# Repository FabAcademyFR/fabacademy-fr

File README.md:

# fabacademy-fr
Studenti Fab Academy 2015 - FabLab Frosinone
hello world

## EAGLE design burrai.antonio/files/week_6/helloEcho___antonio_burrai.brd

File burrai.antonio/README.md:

# fabacademy-fr
Studenti Fabacademy 2015 - FabLab Frosinone
Cartella personale di Antonio Burrai

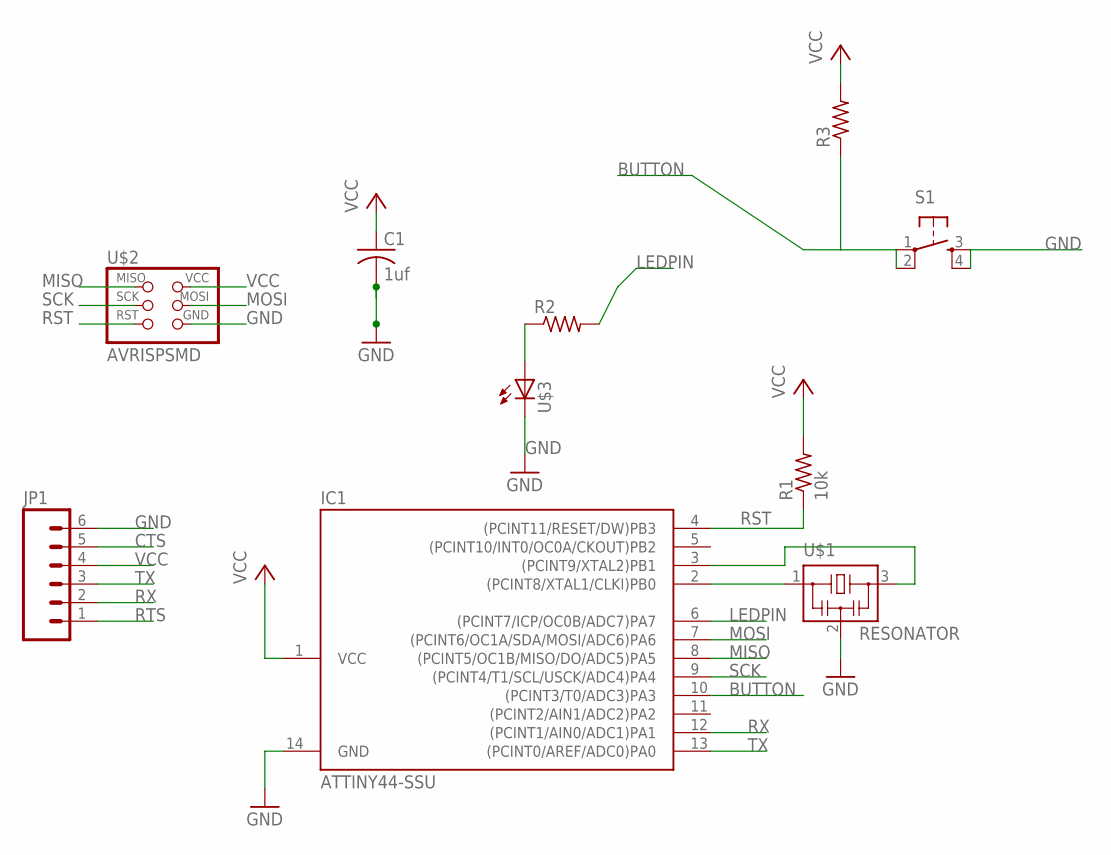
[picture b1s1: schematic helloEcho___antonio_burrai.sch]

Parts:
C1: 1uf; C1206
IC1: ATTINY44-SSU; SOIC14
JP1: M06SMD; 1X06-SMD
R1: 10k; R1206
R2, R3: RESISTOR1206; 1206
S1: 6MM_SWITCH6MM_SWITCH; 6MM_SWITCH
U$1: RESONATOR; EFOBM
U$2: AVRISPSMD; 2X03SMD
U$3: LED1206; 1206

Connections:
BUTTON: IC1.10 ((PCINT3/T0/ADC3)PA3), R3.1, S1.1, S1.2 (P1)
CTS: JP1.5
GND: C1.2, IC1.14 (GND), JP1.6, S1.3 (S), S1.4 (S1), U$1.2, U$2.6 (GND), U$3.2 (C)
LEDPIN: IC1.6 ((PCINT7/ICP/OC0B/ADC7)PA7), R2.2
MISO: IC1.8 ((PCINT5/OC1B/MISO/DO/ADC5)PA5), U$2.1 (MISO)
MOSI: IC1.7 ((PCINT6/OC1A/SDA/MOSI/ADC6)PA6), U$2.4 (MOSI)
unnamed: IC1.2 ((PCINT8/XTAL1/CLKI)PB0), U$1.1
unnamed: IC1.3 ((PCINT9/XTAL2)PB1), U$1.3
unnamed: R2.1, U$3.1 (A)
RST: IC1.4 ((PCINT11/RESET/DW)PB3), R1.1, U$2.5 (RST)
RTS: JP1.1
RX: IC1.12 ((PCINT1/AIN0/ADC1)PA1), JP1.2
SCK: IC1.9 ((PCINT4/T1/SCL/USCK/ADC4)PA4), U$2.3 (SCK)
TX: IC1.13 ((PCINT0/AREF/ADC0)PA0), JP1.3
VCC: C1.1, IC1.1 (VCC), JP1.4, R1.2, R3.2, U$2.2 (VCC)

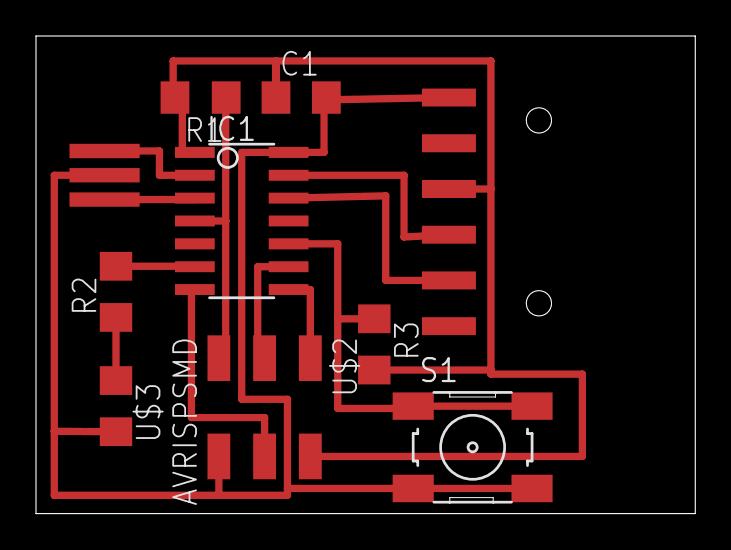
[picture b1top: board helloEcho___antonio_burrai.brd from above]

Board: 1 copper layer, 36.6 x 26.5 mm, 10 parts (0 on the bottom side), 13 nets.

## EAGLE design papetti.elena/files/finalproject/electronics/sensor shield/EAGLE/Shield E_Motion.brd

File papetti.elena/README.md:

# fabacademy-fr
Studenti Fabacademy 2015 - FabLab Frosinone
Cartella personale di Papetti Elena
hello

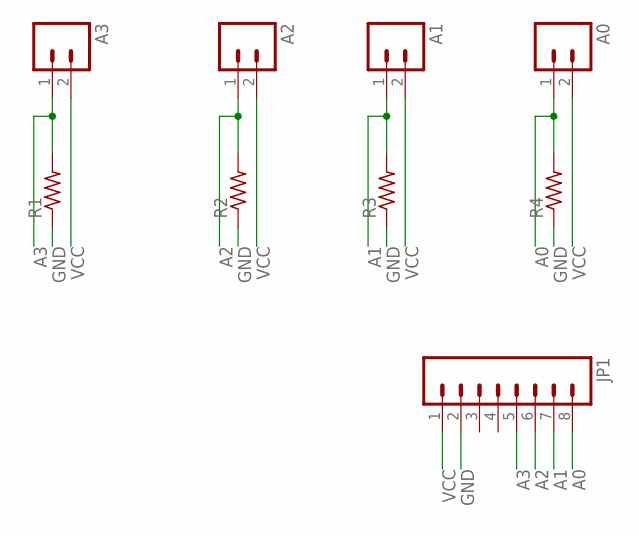
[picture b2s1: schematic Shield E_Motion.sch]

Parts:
A0, A1, A2, A3: M02; 1X02_LONGPADS
JP1: M08LONGPADS; 1X08_LONGPADS
R1, R2, R3, R4: RESISTOR0402; 0402

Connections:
A0: A0.1, JP1.8, R4.2
A1: A1.1, JP1.7, R3.2
A2: A2.1, JP1.6, R2.2
A3: A3.1, JP1.5, R1.2
GND: JP1.2, R1.1, R2.1, R3.1, R4.1
VCC: A0.2, A1.2, A2.2, A3.2, JP1.1

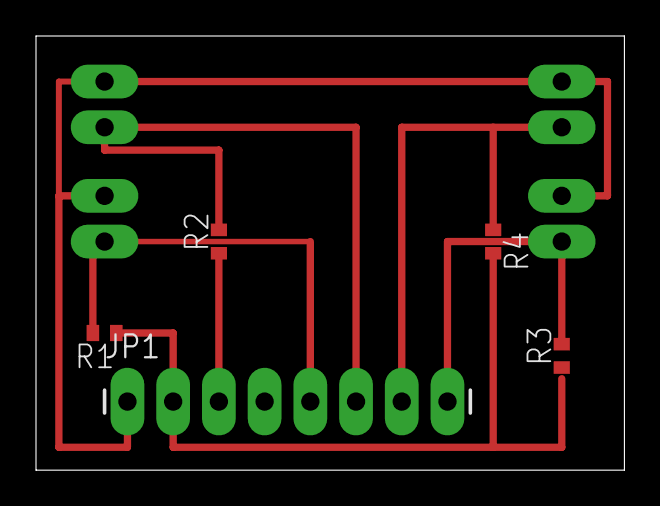
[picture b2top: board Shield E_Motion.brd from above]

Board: 2 copper layers, 32.7 x 24.1 mm, 9 parts (0 on the bottom side), 6 nets.

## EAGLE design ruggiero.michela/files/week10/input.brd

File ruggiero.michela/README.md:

# fabacademy-fr
Studenti Fabacademy 2015 - FabLab Frosinone
Cartella personale di Ruggiero Michela

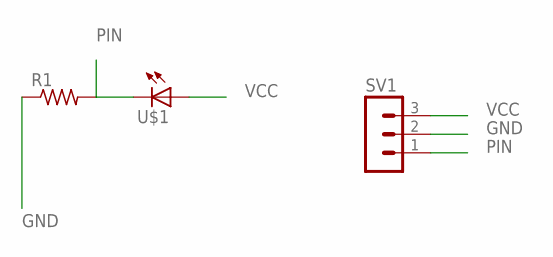
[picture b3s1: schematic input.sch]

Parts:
R1: RESISTOR1206; 1206
SV1: MA03-1
U$1: LED5MM; 5MM

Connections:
GND: R1.1, SV1.2
PIN: R1.2, SV1.1, U$1.OUT (C)
VCC: SV1.3, U$1.IN (A)

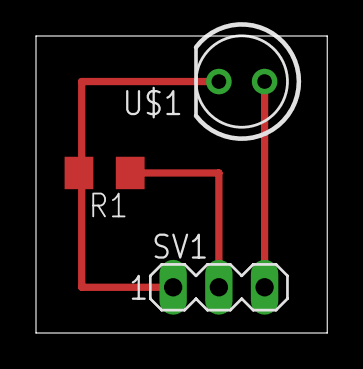
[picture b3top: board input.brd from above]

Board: 2 copper layers, 16.2 x 16.5 mm, 3 parts (0 on the bottom side), 3 nets.

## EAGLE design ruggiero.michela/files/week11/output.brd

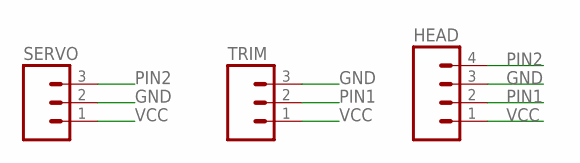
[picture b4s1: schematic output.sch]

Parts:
HEAD: M04LONGPADS; 1X04_LONGPADS
SERVO: M03PTH; 1X03
TRIM: M03PTH; 1X03

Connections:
GND: HEAD.3, SERVO.2, TRIM.3
PIN1: HEAD.2, TRIM.2
PIN2: HEAD.4, SERVO.3
VCC: HEAD.1, SERVO.1, TRIM.1

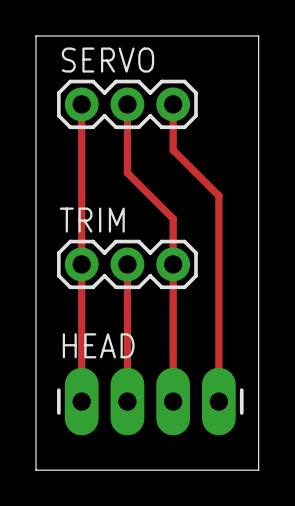
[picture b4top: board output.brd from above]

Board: 2 copper layers, 12.4 x 24.1 mm, 3 parts (0 on the bottom side), 4 nets.

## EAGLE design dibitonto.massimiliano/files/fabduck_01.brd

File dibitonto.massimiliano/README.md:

# fabacademy-fr
Studenti Fabacademy 2015 - FabLab Frosinone
Cartella personale di Dibitonto Massimiliano

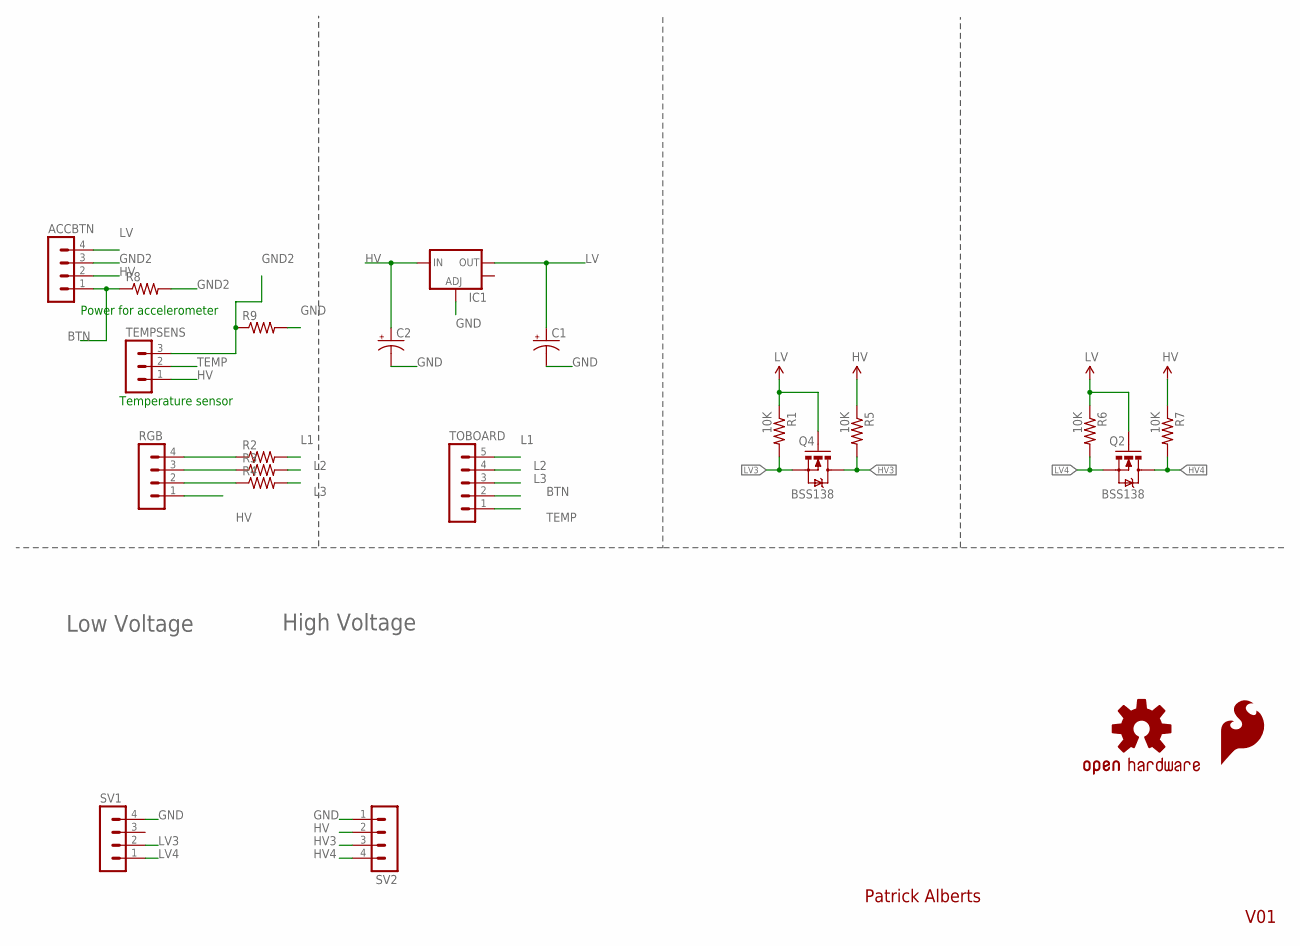
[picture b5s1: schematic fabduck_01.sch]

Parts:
ACCBTN: MA04-1
C1, C2: CAP_POLD; PANASONIC_D
IC1: V_REG_LM1117SOT223; SOT223
LOGO1: SFE_LOGO_FLAME.1_INCH; SFE_LOGO_FLAME_.1
LOGO2: OSHW-LOGOS; OSHW-LOGO-S
Q2, Q4: BSS138; SOT23-3
R1, R5, R6, R7: 10K; 0603-RES
R2, R3, R4, R8, R9: RESISTOR1206; 1206
RGB: MA04-1
SV1, SV2: MA04-1
TEMPSENS: MA03-1
TOBOARD: MA05-1

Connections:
BTN: ACCBTN.1, R8.1, TOBOARD.2
GND: C1.-, C2.-, IC1.1 (ADJ), R9.2, SV1.4, SV2.1
GND2: ACCBTN.3, R8.2, R9.1, TEMPSENS.3
HV: ACCBTN.2, C2.+, IC1.3 (IN), R5.1, R7.1, RGB.1, SV2.2, TEMPSENS.1
HV3: Q4.3 (D), R5.2, SV2.3
HV4: Q2.3 (D), R7.2, SV2.4
L1: R2.2, TOBOARD.5
L2: R3.2, TOBOARD.4
L3: R4.2, TOBOARD.3
LV: ACCBTN.4, C1.+, IC1.2 (OUT), Q2.1 (G), Q4.1 (G), R1.1, R6.1
LV3: Q4.2 (S), R1.2, SV1.2
LV4: Q2.2 (S), R6.2, SV1.1
unnamed: R3.1, RGB.3
unnamed: R4.1, RGB.2
unnamed: R2.1, RGB.4
TEMP: TEMPSENS.2, TOBOARD.1

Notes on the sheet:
High Voltage
Low Voltage
V01
Patrick Alberts
Power for accelerometer
Temperature sensor

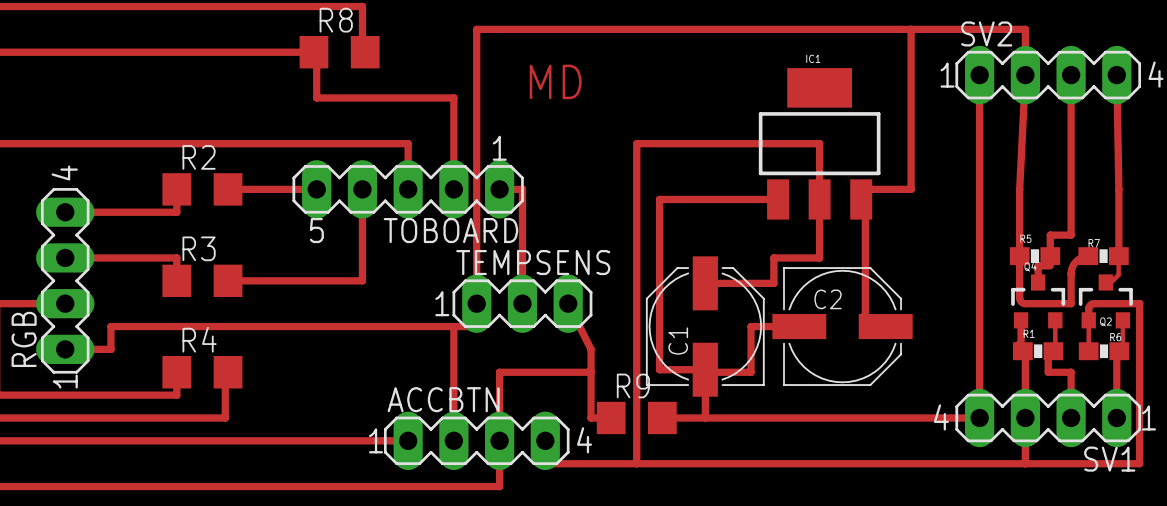
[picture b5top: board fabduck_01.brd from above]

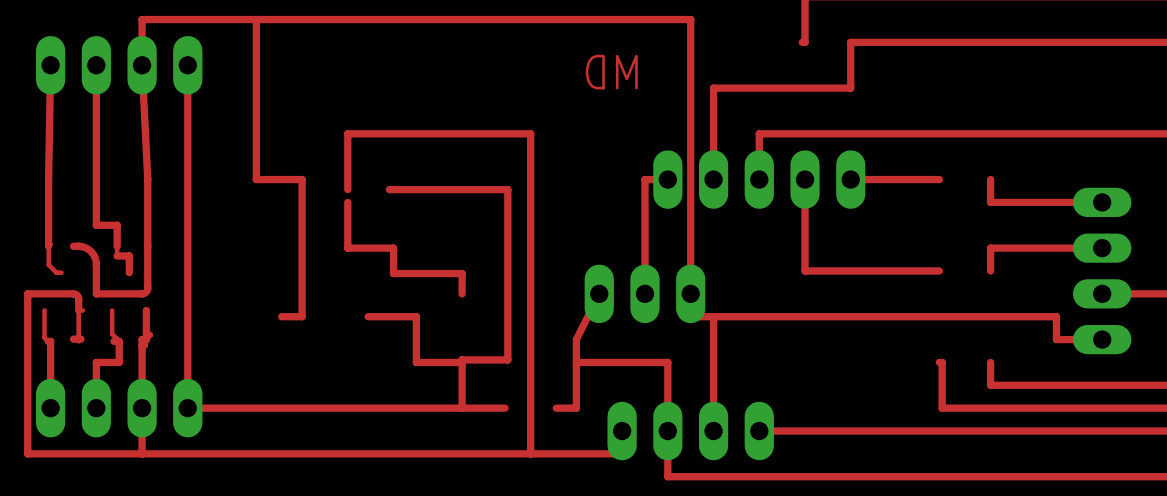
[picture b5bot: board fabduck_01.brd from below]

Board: 2 copper layers, 22 parts (2 on the bottom side), 16 nets.

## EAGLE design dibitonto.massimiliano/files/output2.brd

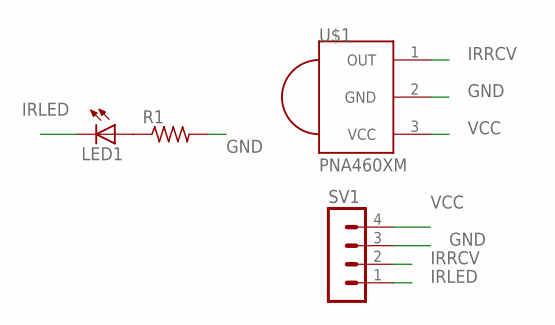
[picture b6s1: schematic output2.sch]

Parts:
LED1: LED5MM
R1: RESISTOR1206; 1206
SV1: MA04-1
U$1: PNA460XM

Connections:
GND: R1.2, SV1.3, U$1.2 (GND)
IRLED: LED1.K (C), SV1.1
IRRCV: SV1.2, U$1.1 (OUT)
LDR: LED1.A, R1.1
VCC: SV1.4, U$1.3 (VCC)

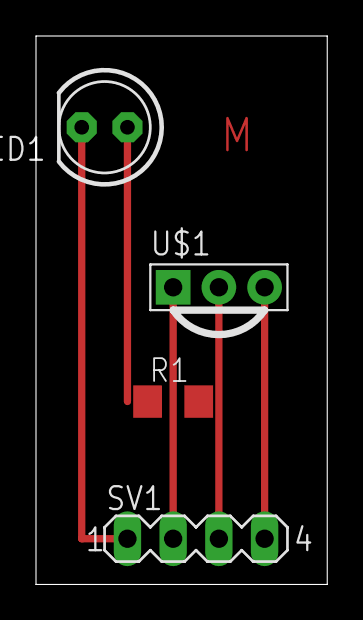
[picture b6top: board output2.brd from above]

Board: 2 copper layers, 16.2 x 30.5 mm, 4 parts (0 on the bottom side), 5 nets.

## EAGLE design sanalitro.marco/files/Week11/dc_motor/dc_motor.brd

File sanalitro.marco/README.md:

# fabacademy-fr
Studenti Fabacademy 2015 - FabLab Frosinone
Cartella personale di Sanalitro Marco

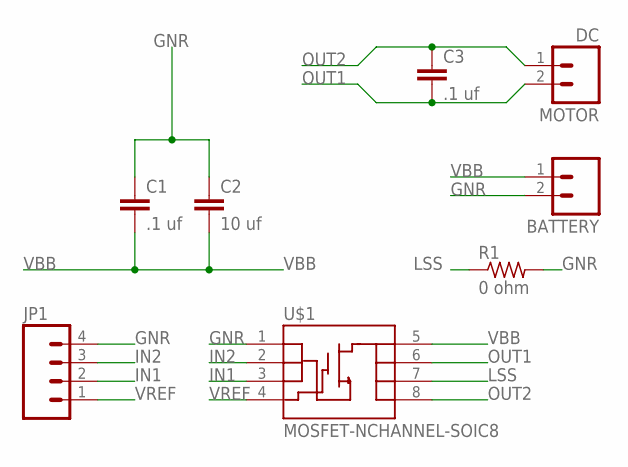
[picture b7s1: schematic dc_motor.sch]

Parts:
BATTERY: M02; 1X02_LONGPADS
C1, C3: .1 uf; 1206
C2: 10 uf; 1206
JP1: M04LONGPADS; 1X04_LONGPADS
MOTOR: DC; 1X02_LONGPADS
R1: 0 ohm; 1206
U$1: MOSFET-NCHANNEL-SOIC8; SO08

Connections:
GNR: BATTERY.2, C1.1, C2.1, JP1.4, R1.2, U$1.1 (S)
IN1: JP1.2, U$1.3 (S)
IN2: JP1.3, U$1.2 (S)
LSS: R1.1, U$1.7 (D)
OUT1: C3.2, MOTOR.2, U$1.6 (D)
OUT2: C3.1, MOTOR.1, U$1.8 (D)
VBB: BATTERY.1, C1.2, C2.2, U$1.5 (D)
VREF: JP1.1, U$1.4 (G)

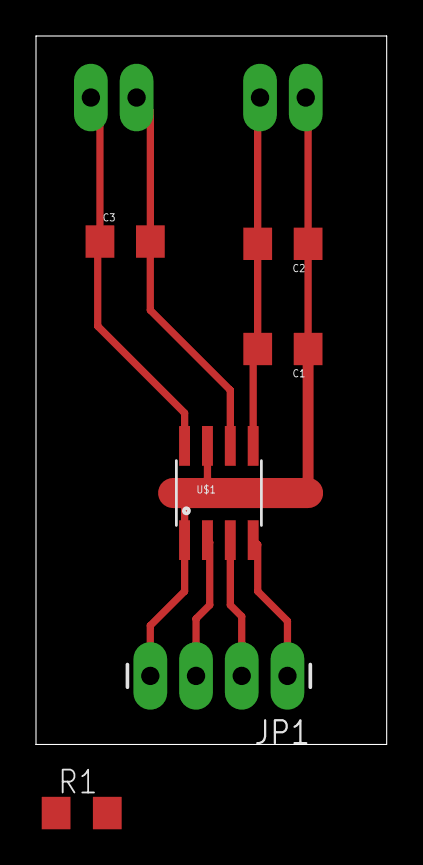
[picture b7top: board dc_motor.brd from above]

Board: 2 copper layers, 19.5 x 39.4 mm, 8 parts (0 on the bottom side), 8 nets.

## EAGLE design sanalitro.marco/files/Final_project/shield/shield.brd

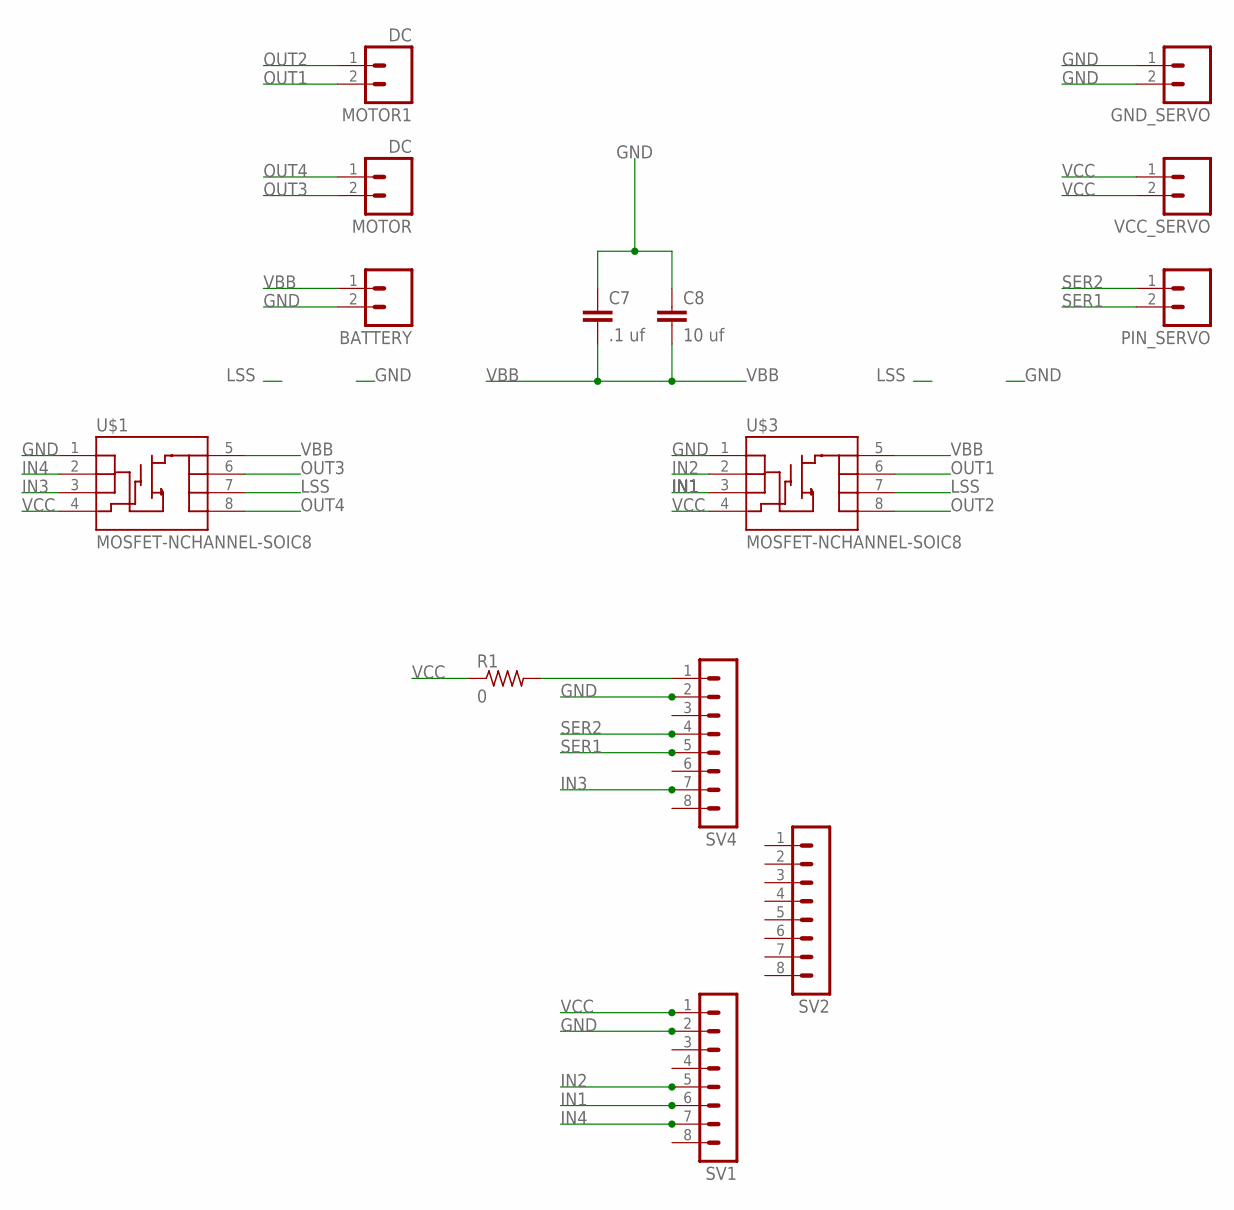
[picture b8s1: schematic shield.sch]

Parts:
BATTERY: M02; 1X02_LONGPADS
C7: .1 uf; 1206
C8: 10 uf; 1206
GND_SERVO: M02; 1X02_LONGPADS
MOTOR, MOTOR1: DC; 1X02_LONGPADS
PIN_SERVO: M02; 1X02_LONGPADS
R1: 0; 1206
SV1, SV2, SV4: MA08-1
U$1, U$3: MOSFET-NCHANNEL-SOIC8; SO08
VCC_SERVO: M02; 1X02_LONGPADS

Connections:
GND: BATTERY.2, C7.1, C8.1, GND_SERVO.1, GND_SERVO.2, SV1.2, SV4.2, U$1.1 (S), U$3.1 (S)
IN1: SV1.6, U$3.3 (S)
IN2: SV1.5, U$3.2 (S)
IN3: SV4.7, U$1.3 (S)
IN4: SV1.7, U$1.2 (S)
LSS: U$1.7 (D), U$3.7 (D)
unnamed: R1.2, SV4.1
OUT1: MOTOR1.2, U$3.6 (D)
OUT2: MOTOR1.1, U$3.8 (D)
OUT3: MOTOR.2, U$1.6 (D)
OUT4: MOTOR.1, U$1.8 (D)
SER1: PIN_SERVO.2, SV4.5
SER2: PIN_SERVO.1, SV4.4
VBB: BATTERY.1, C7.2, C8.2, U$1.5 (D), U$3.5 (D)
VCC: R1.1, SV1.1, U$1.4 (G), U$3.4 (G), VCC_SERVO.1, VCC_SERVO.2

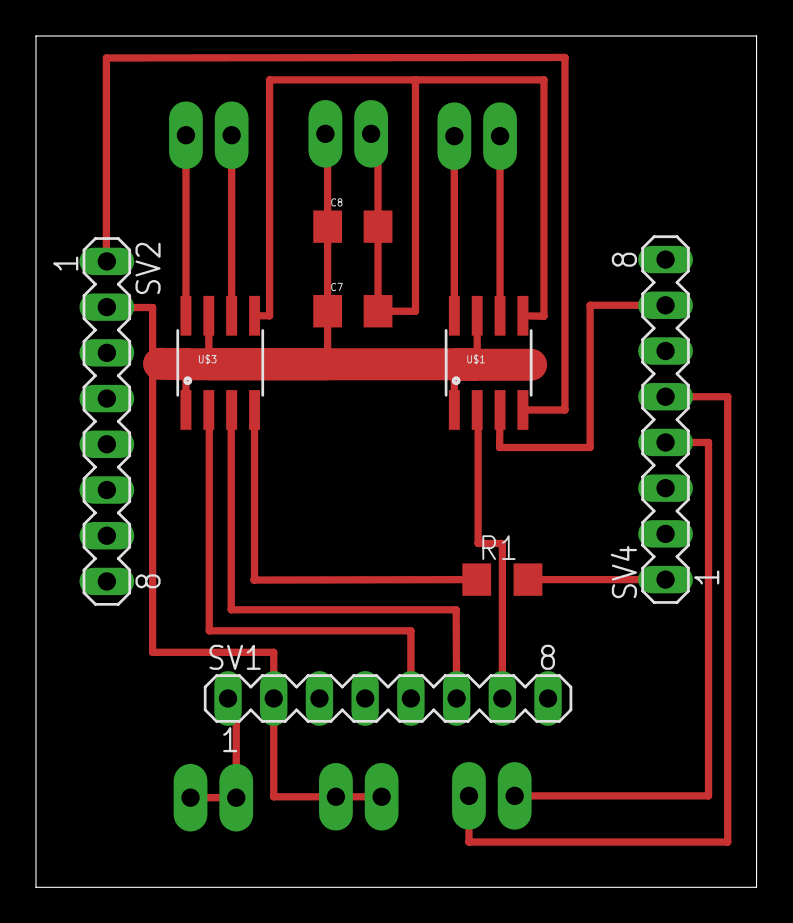
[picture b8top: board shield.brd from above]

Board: 2 copper layers, 40.0 x 47.3 mm, 14 parts (0 on the bottom side), 15 nets.

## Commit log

2015-02-01 Init
2015-02-01 inizializzazione repository
2015-02-02 test
2015-02-02 test2
2015-02-02 test3
2015-02-02 test4
2015-02-02 test5
2015-02-03 Week 1 assignment
2015-02-03 Final project idea
2015-02-03 week1
2015-02-03 Added WEEK1 assignment
2015-02-03 week1 aggiornamento
2015-02-04 Right directory tree
2015-02-06 change week1
2015-02-10 Second week upload
2015-02-10 Second week upload - 3D models added
2015-02-10 WEEK2 assignment and better website
2015-02-10 Week2
2015-02-10 upload 2 week
2015-02-11 firstupload
2015-02-11 firstweek
2015-02-13 thirdweek
2015-02-17 Computer Controlled Cutting
2015-02-17 Week 3 update
2015-02-17 Wee3
2015-02-17 Week3
2015-02-17 small size of all folders. No Assignment 3
2015-02-17 Week3 upload
2015-02-17 aggiornamento week3
2015-03-03 4 and 5 week and final project update
2015-03-03 Week5
2015-03-03 upload W4-W5
2015-03-03 Week5scanandprint
2015-03-03 update w4
2015-03-04 Week3 and Week5 scan part
2015-03-04 Week5 Printing part
2015-03-04 addWeek5
2015-03-10 6 week - Electronics production
2015-03-10 Week6
2015-03-10 upload week6
2015-03-17 Embedded programming and idea update
2015-03-18 Week7
2015-03-24 week8
2015-03-24 upload week 8
2015-04-07 Boring Stuff
2015-04-07 week9
2015-04-07 Update assignment 7,8 and 9
2015-04-07 temporary upload week9
2015-04-08 week 9 part1
2015-04-08 index correction
2015-04-08 index mistake
2015-04-08 last is coming
2015-04-08 final9 and early8
2015-04-14 Input devices assignment
2015-04-14 week10
2015-04-14 upload week 10 and update webpage
2015-04-15 Upgrade week 10
2015-04-20 MEGA UPLOAD
2015-04-21 Output assignment
2015-04-21 week11
2015-04-21 upload week11
2015-04-22 recovery upload w 11
2015-04-22 Output update
2015-04-28 upload week 12
2015-04-28 update week 11 and 12
2015-05-05 week13
2015-05-05 upload week 13
2015-05-12 week14
2015-05-12 Update week 13 and 10
2015-05-12 week4index
2015-05-12 upload updates and files
2015-05-18 week15,week12nf
2015-05-18 updating 18/05
2015-05-18 Applications and implications and other updates
2015-05-19 week15
2015-05-19 final project 19 may
2015-05-19 modifiedImage
2015-05-19 solving problems
2015-05-19 upload week15
2015-05-26 Final project and other updates
2015-05-26 update week 15
2015-05-26 ass. 1 to 12 and 15 uploaded
2015-05-26 marco
2015-06-02 Presentation slide and final project update
2015-06-02 update files and machining
2015-06-02 Slide
2015-06-02 week17
2015-06-02 Presentation
2015-06-02 Elena Presentation
2015-06-02 up.zac.
2015-06-07 final project update
2015-06-07 video and slide update
2015-06-08 presentattion
2015-06-08 video update
2015-06-08 final push for 10/06
2015-06-09 bio-png
2015-06-09 upload presentation
2015-06-09 video
2015-06-09 video new
2015-06-09 best video
2015-06-09 new presentation
2015-06-09 png update
2015-06-09 presentation white
2015-06-09 updated video
2015-06-19 mechanical
2015-06-19 week19
2015-06-19 week20
2015-06-19 upload week16
2015-06-22 1 to 10 reviewed
2015-06-24 upload generale
2015-06-24 2,3,5,6
2015-06-24 upload generale2
2015-06-25 update 25 jun
2015-06-25 upload generale 3
2015-06-25 upload 26 jun
2015-06-26 output and interfaces
2015-06-26 upload 4 por favor
2015-06-26 miky
2015-06-27 under 25MB
2015-06-27 almost done
2015-06-27 upload 5
2015-06-27 6,9,10,14
2015-06-27 upload 6
2015-06-27 weeks
2015-06-28 week 13
2015-06-28 vynil
2015-06-28 4,18,parte16,17
2015-06-28 first Mauro revision
2015-06-28 upload post review
2015-06-28 week 17
2015-06-28 fixes after review
2015-06-28 broken link fixes
2015-06-28 interface
2015-06-28 file
2015-06-28 files
2015-06-28 1,12,16,17,18
2015-06-29 final push
2015-06-29 week18
2015-06-30 finalP
2015-06-30 final project1
2015-06-30 Finito
2015-06-30 final prject prima parte
2015-06-30 f proj parte 2
2015-06-30 f proj parte3
2015-06-30 upload finale
2015-06-30 broken image on final project
2015-07-01 update eventually
2015-07-16 cartella files
2015-07-16 Files folder added
2015-07-16 files folder update

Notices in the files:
parts and their libraries:
SparkFun-Aesthetics: Licensing: CC v3.0 Share-Alike You are welcome to use this library for commercial purposes.
SparkFun-Aesthetics: Released under the Creative Commons
SparkFun-Aesthetics: http://creativecommons.org/licenses/by-sa/3.0
